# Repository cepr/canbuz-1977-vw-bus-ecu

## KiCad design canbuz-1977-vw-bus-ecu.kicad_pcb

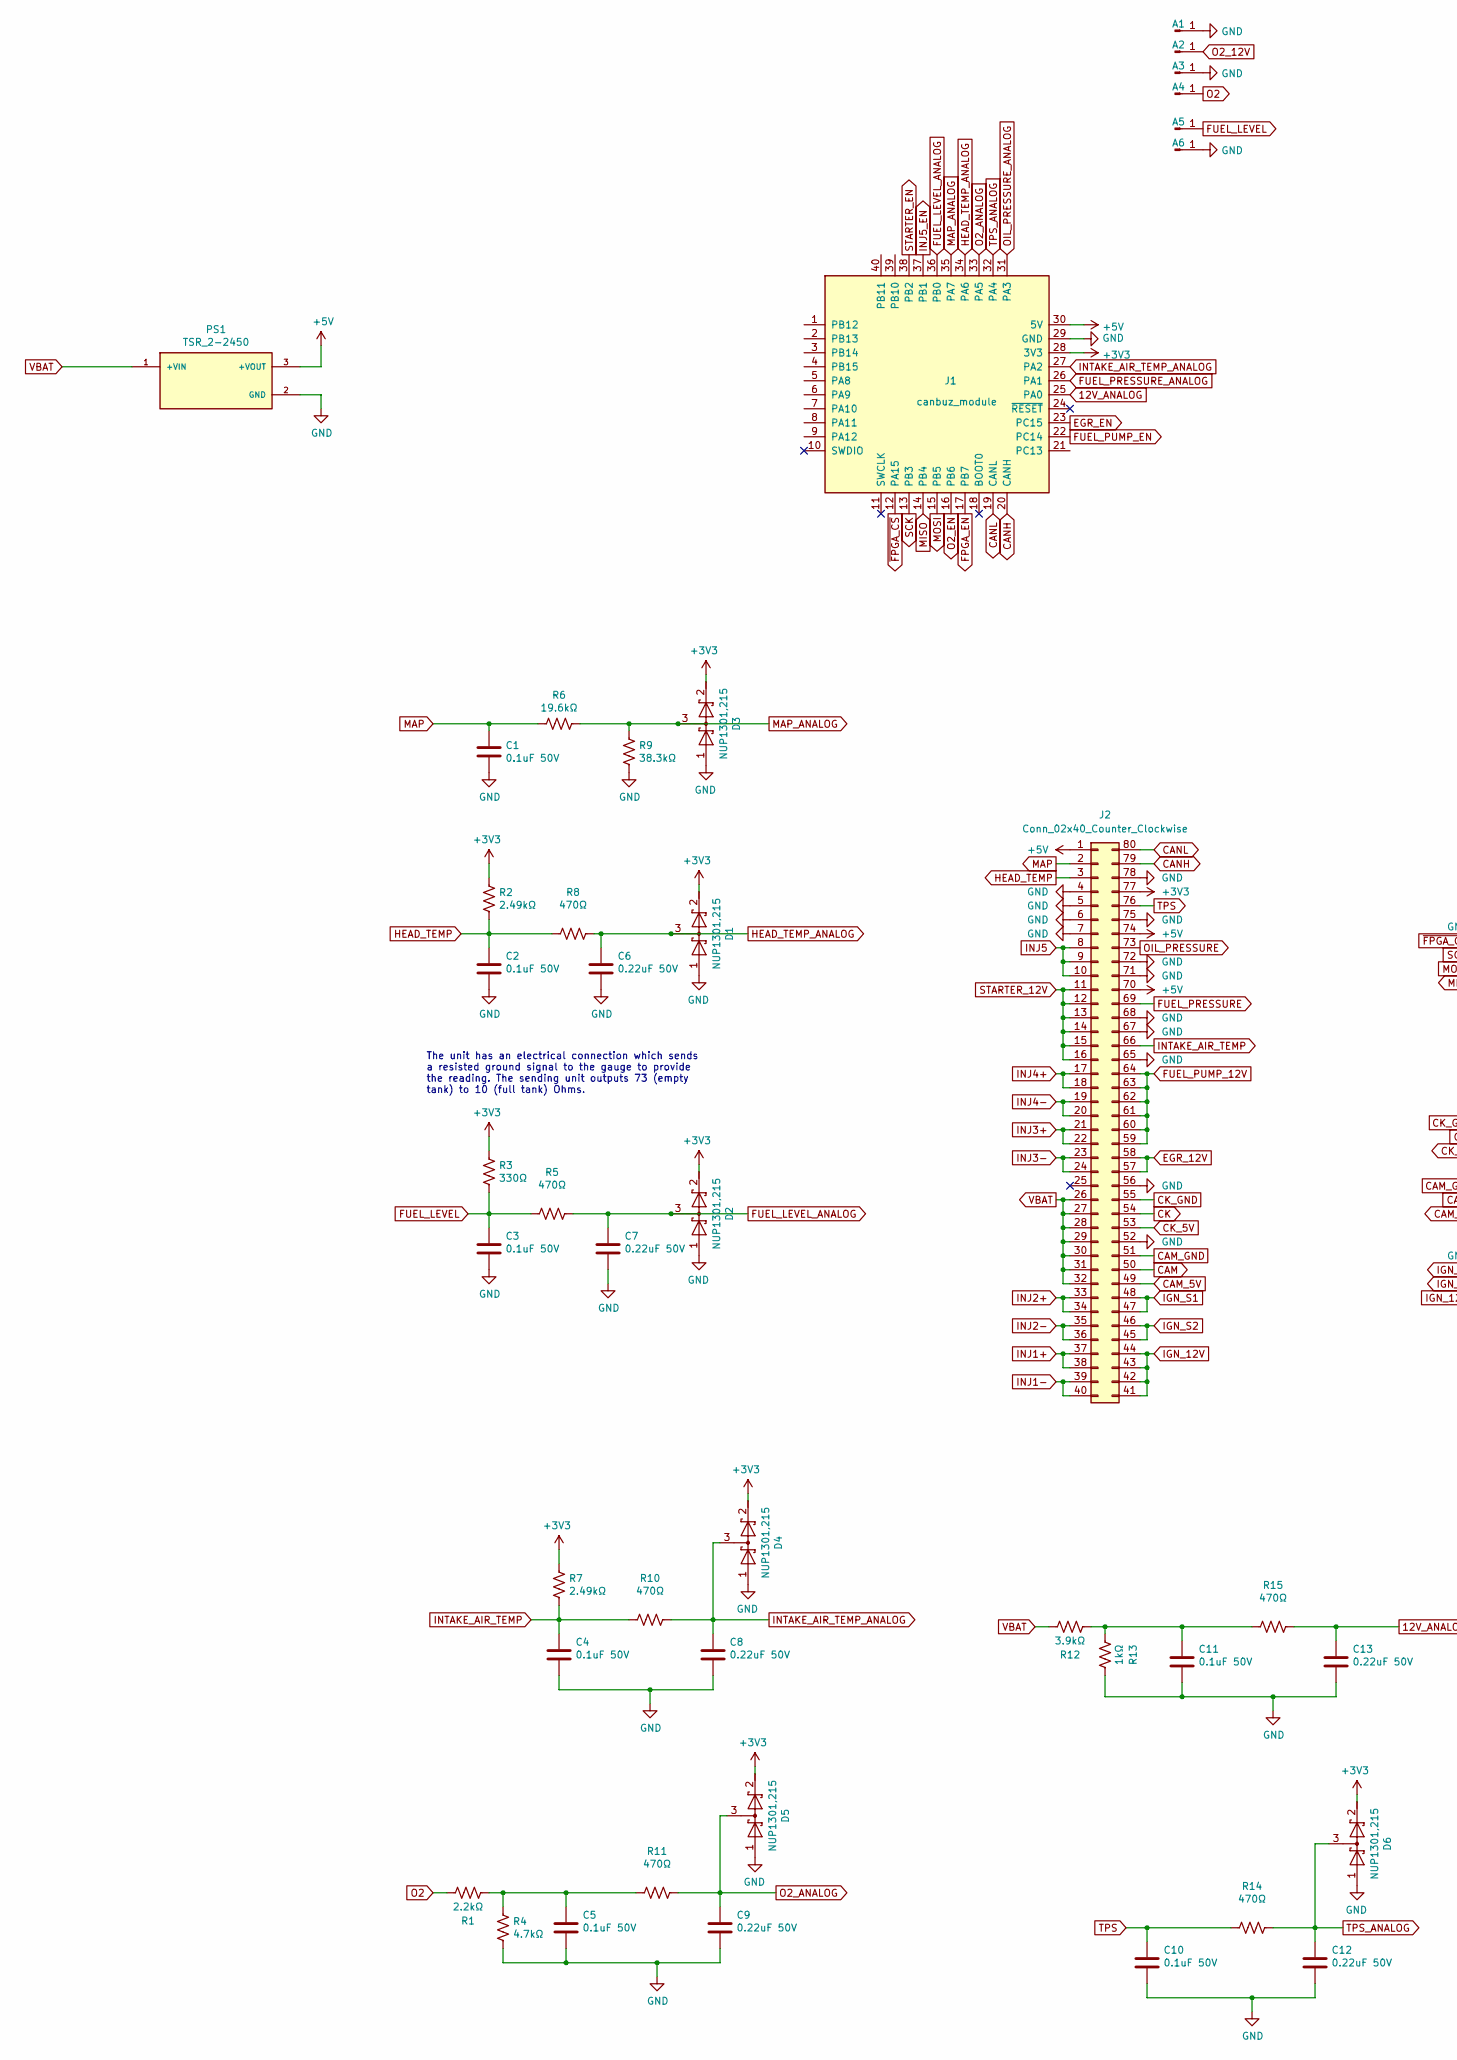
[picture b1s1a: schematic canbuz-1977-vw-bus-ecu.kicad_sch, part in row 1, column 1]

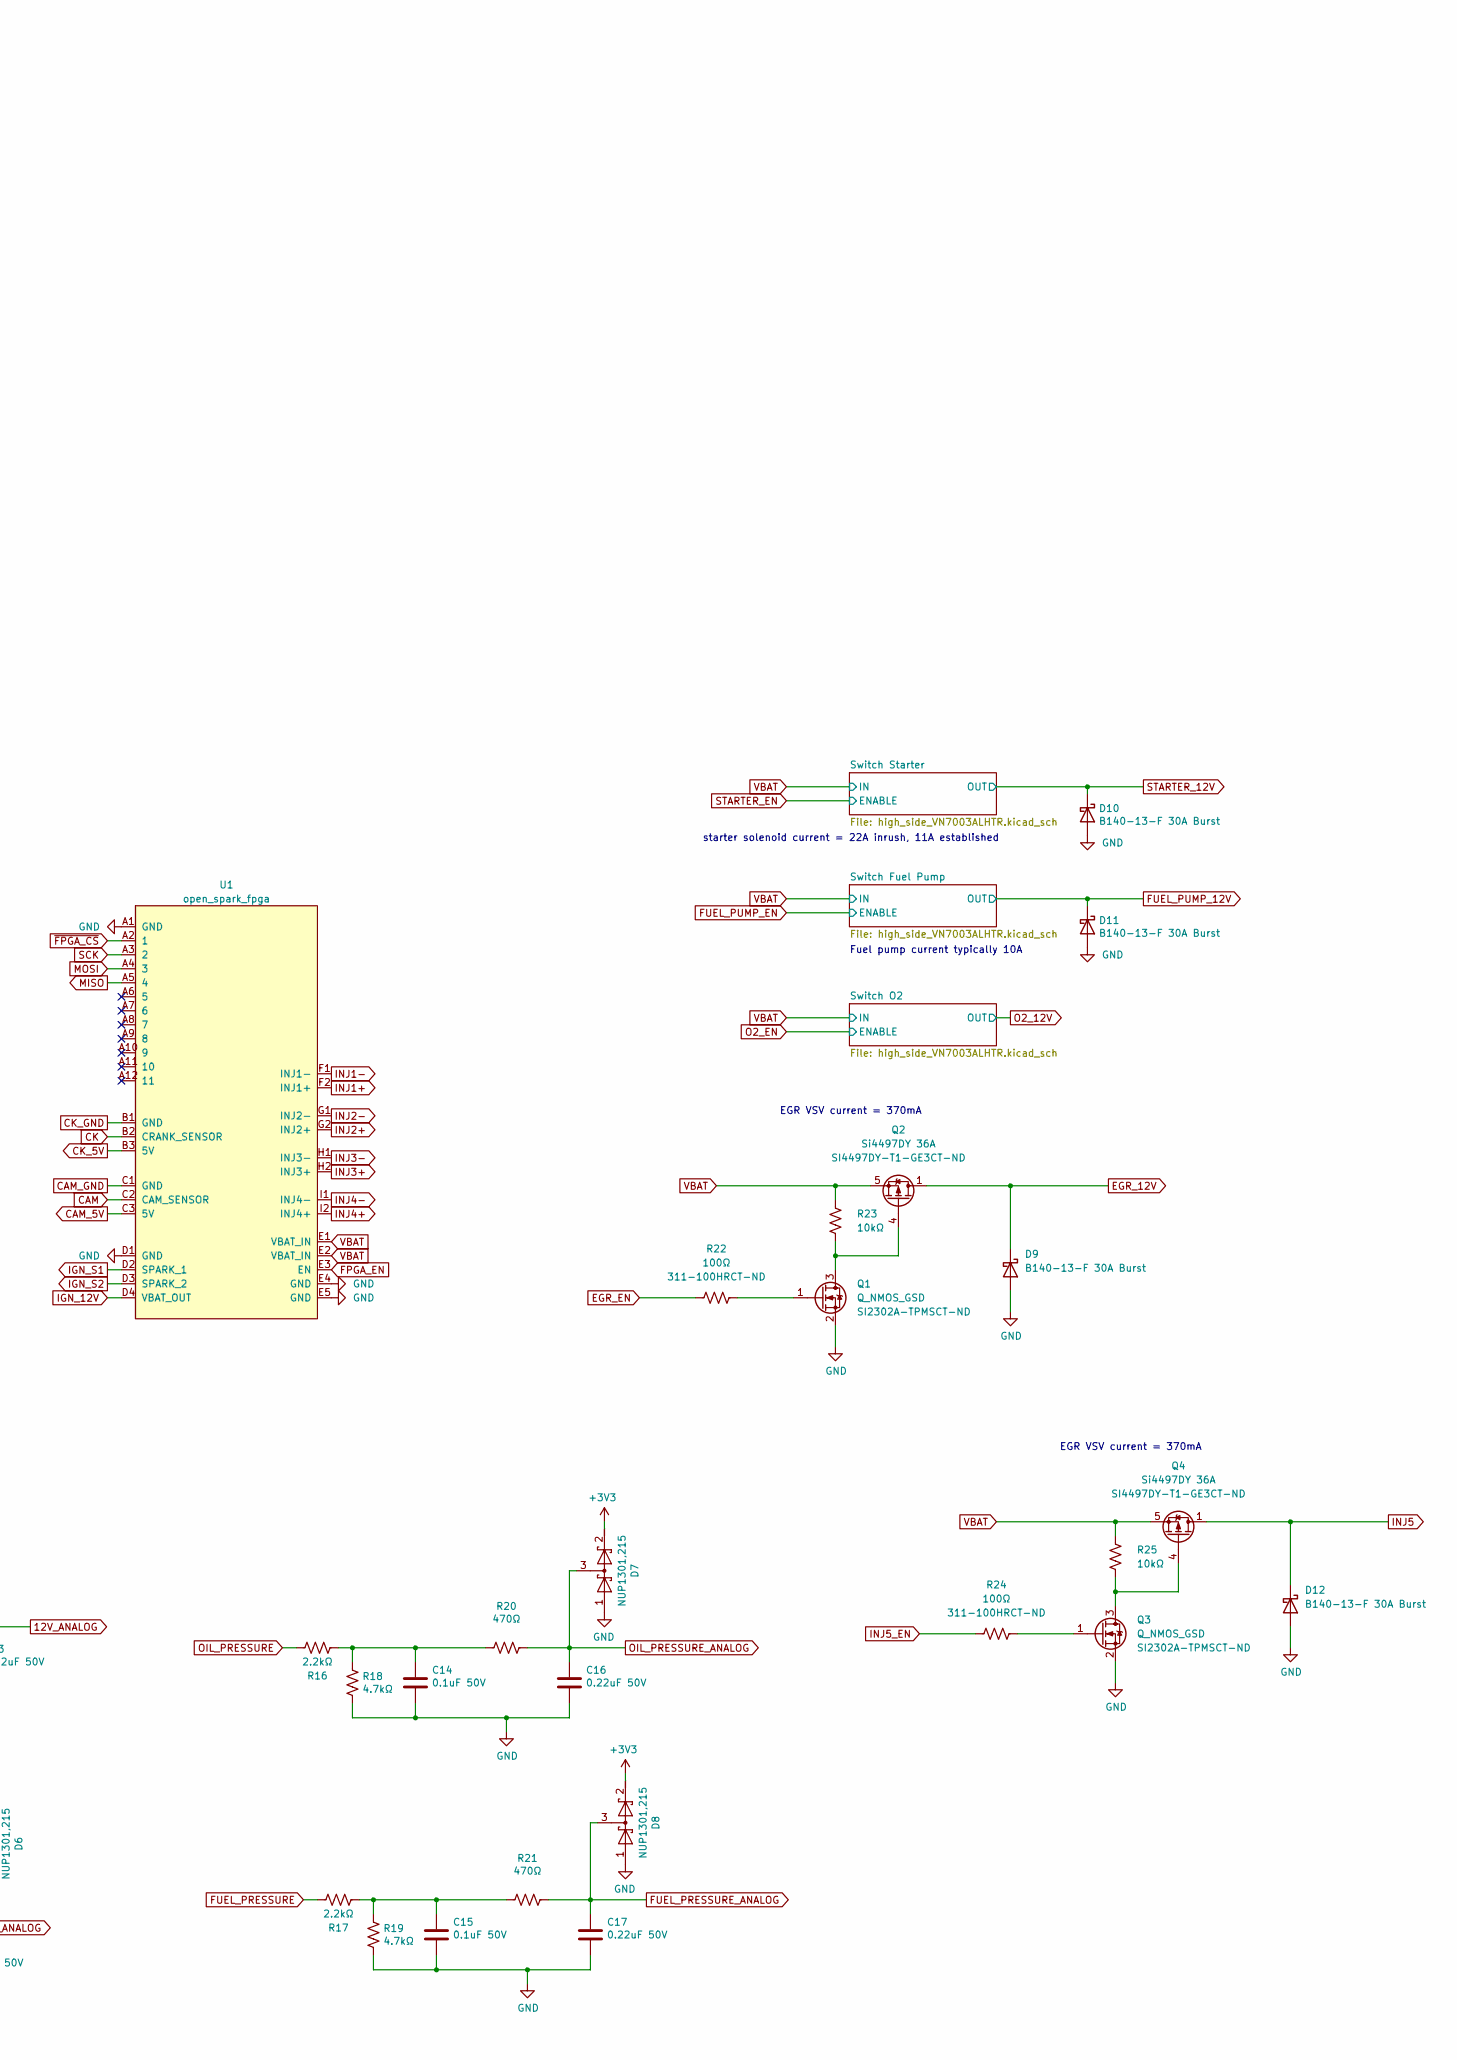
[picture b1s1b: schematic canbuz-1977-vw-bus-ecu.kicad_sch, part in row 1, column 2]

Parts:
A1, A2, A3, A4, A5, A6: Spade_Male
C1, C2, C3, C4, C5, C10, C11, C14, C15: 0.1uF 50V; C_0805_2012Metric_Pad1.18x1.45mm_HandSolder; Part KAF21BR71H104KT; DigiKey 478-6048-1-ND
C6, C7, C8, C9, C12, C13, C16, C17: 0.22uF 50V; C_0805_2012Metric_Pad1.18x1.45mm_HandSolder; Part CGA4J2X7R1H224K125AA; DigiKey 445-5683-1-ND
D1, D2, D3, D4, D5, D6, D7, D8: NUP1301,215; SOT-23; Part NUP1301,215; DigiKey 1727-5056-1-ND
D9, D10, D11, D12: B140-13-F 30A Burst; D_SMA; Part B340A-13-F
J1: canbuz_module; canbuz-module
J2: Conn_02x40_Counter_Clockwise; canbuz-1977-vw-bus-ecu-connector
PS1: TSR_2-2450; CONV_TSR_2-2450; Part TSR 2-2450; DigiKey 1951-2692-ND
Q1, Q3: Q_NMOS_GSD; SOT-23; Part SI2302A-TP; DigiKey SI2302A-TPMSCT-ND
Q2, Q4: Si4497DY 36A; SO-8_3.9x4.9mm_P1.27mm; Part SI4497DY-T1-GE3; DigiKey SI4497DY-T1-GE3CT-ND
R1, R16, R17: 2.2kΩ; R_0603_1608Metric_Pad0.98x0.95mm_HandSolder; Part ERJ-3GEYJ222V
R2, R7: 2.49kΩ; R_0603_1608Metric_Pad0.98x0.95mm_HandSolder; Part RK73H1JTTD2491F
R3: 330Ω; R_0603_1608Metric_Pad0.98x0.95mm_HandSolder
R4, R18, R19: 4.7kΩ; R_0603_1608Metric_Pad0.98x0.95mm_HandSolder; Part RC0603FR-074K7L
R5, R8, R10, R11, R14, R15, R20, R21: 470Ω; R_0603_1608Metric_Pad0.98x0.95mm_HandSolder; Part RC0603JR-07470RL
R6: 19.6kΩ; R_0603_1608Metric_Pad0.98x0.95mm_HandSolder; Part RC0603FR-0719K6L
R9: 38.3kΩ; R_0603_1608Metric_Pad0.98x0.95mm_HandSolder; Part RC0603FR-0738K3L
R12: 3.9kΩ; R_0603_1608Metric_Pad0.98x0.95mm_HandSolder; Part RC0603FR-073K9L
R13: 1kΩ; R_0603_1608Metric_Pad0.98x0.95mm_HandSolder; Part RC0603FR-071KL
R22, R24: 100Ω; R_0603_1608Metric_Pad0.98x0.95mm_HandSolder; Part RC0603FR-07100RL; DigiKey 311-100HRCT-ND
R23, R25: 10kΩ; R_0603_1608Metric_Pad0.98x0.95mm_HandSolder; Part RC0603FR-0710KL
U1: open_spark_fpga

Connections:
12V_ANALOG: C13.1, J1.25 (PA0), R15.1
+3V3: D1.2 (K), D2.2 (K), D3.2 (K), D4.2 (K), D5.2 (K), D6.2 (K), D7.2 (K), D8.2 (K), J1.28 (3V3), J2.77, R2.2, R3.2, R7.2
+5V: J1.30 (5V), J2.1, J2.70, J2.74, PS1.3 (+VOUT)
CAM: J2.50, U1.C2 (CAM_SENSOR)
CAM_5V: J2.49, U1.C3 (5V)
CAM_GND: J2.51, U1.C1 (GND)
CANH: J1.20 (CANH), J2.79
CANL: J1.19 (CANL), J2.80
CK: J2.54, U1.B2 (CRANK_SENSOR)
CK_5V: J2.53, U1.B3 (5V)
CK_GND: J2.55, U1.B1 (GND)
EGR_12V: D9.1 (K), J2.57, J2.58, Q2.1 (D), Q2.2 (D), Q2.3 (D)
EGR_EN: J1.23 (PC15), R22.1
FPGA_EN: J1.17 (PB7), U1.E3 (EN)
FUEL_LEVEL: A5.1, C3.1, R3.1, R5.2
FUEL_LEVEL_ANALOG: C7.1, D2.3 (common), J1.36 (PB0), R5.1
FUEL_PRESSURE: J2.69, R17.1
FUEL_PRESSURE_ANALOG: C17.1, D8.3 (common), J1.26 (PA1), R21.1
FUEL_PUMP_12V: D11.1 (K), J2.59, J2.60, J2.61, J2.62, J2.63, J2.64; also elsewhere on the board
FUEL_PUMP_EN: J1.22 (PC14); also elsewhere on the board
GND: A1.1, A3.1, A6.1, C1.2, C2.2, C3.2, C4.2, C5.2, C6.2, C7.2, C8.2, C9.2, C10.2, C11.2, C12.2, C13.2, C14.2, C15.2, C16.2, C17.2, D1.1 (A), D2.1 (A), D3.1 (A), D4.1 (A), D5.1 (A), D6.1 (A), D7.1 (A), D8.1 (A), D9.2 (A), D10.2 (A), D11.2 (A), D12.2 (A), J1.29 (GND), J2.4, J2.5, J2.6, J2.7, J2.52, J2.56, J2.65, J2.67, J2.68, J2.71, J2.72, J2.75, J2.78, PS1.2 (GND), Q1.2 (S), Q3.2 (S), R4.1, R9.2, R13.1, R18.1, R19.1, U1.A1 (GND), U1.D1 (GND), U1.E4 (GND), U1.E5 (GND); also elsewhere on the board
HEAD_TEMP: C2.1, J2.3, R2.1, R8.2
HEAD_TEMP_ANALOG: C6.1, D1.3 (common), J1.34 (PA6), R8.1
IGN_12V: J2.41, J2.42, J2.43, J2.44, U1.D4 (VBAT_OUT)
IGN_S1: J2.47, J2.48, U1.D2 (SPARK_1)
IGN_S2: J2.45, J2.46, U1.D3 (SPARK_2)
INJ1+: J2.37, J2.38, U1.F2 (INJ1+)
INJ1-: J2.39, J2.40, U1.F1 (INJ1-)
INJ2+: J2.33, J2.34, U1.G2 (INJ2+)
INJ2-: J2.35, J2.36, U1.G1 (INJ2-)
INJ3+: J2.21, J2.22, U1.H2 (INJ3+)
INJ3-: J2.23, J2.24, U1.H1 (INJ3-)
INJ4+: J2.17, J2.18, U1.I2 (INJ4+)
INJ4-: J2.19, J2.20, U1.I1 (INJ4-)
INJ5: D12.1 (K), J2.8, J2.9, J2.10, Q4.1 (D), Q4.2 (D), Q4.3 (D)
INJ5_EN: J1.37 (PB1), R24.1
INTAKE_AIR_TEMP: C4.1, J2.66, R7.1, R10.2
INTAKE_AIR_TEMP_ANALOG: C8.1, D4.3 (common), J1.27 (PA2), R10.1
MAP: C1.1, J2.2, R6.2
MAP_ANALOG: D3.3 (common), J1.35 (PA7), R6.1, R9.1
MISO: J1.14 (PB4), U1.A5 (4)
MOSI: J1.15 (PB5), U1.A4 (3)
unnamed: C5.1, R1.2, R4.2, R11.2
unnamed: C11.1, R12.2, R13.2, R15.2
unnamed: C14.1, R16.2, R18.2, R20.2
unnamed: C15.1, R17.2, R19.2, R21.2
unnamed: Q1.1 (G), R22.2
unnamed: Q1.3 (D), Q2.4 (G), R23.1
unnamed: Q3.1 (G), R24.2
unnamed: Q3.3 (D), Q4.4 (G), R25.1
O2: A4.1, R1.1
O2_12V: A2.1; also elsewhere on the board
O2_ANALOG: C9.1, D5.3 (common), J1.33 (PA5), R11.1
O2_EN: J1.16 (PB6); also elsewhere on the board
OIL_PRESSURE: J2.73, R16.1
OIL_PRESSURE_ANALOG: C16.1, D7.3 (common), J1.31 (PA3), R20.1
SCK: J1.13 (PB3), U1.A3 (2)
STARTER_12V: D10.1 (K), J2.11, J2.12, J2.13, J2.14, J2.15, J2.16; also elsewhere on the board
STARTER_EN: J1.38 (PB2); also elsewhere on the board
TPS: C10.1, J2.76, R14.2
TPS_ANALOG: C12.1, D6.3 (common), J1.32 (PA4), R14.1
VBAT: J2.26, J2.27, J2.28, J2.29, J2.30, J2.31, J2.32, PS1.1 (+VIN), Q2.5 (S), Q2.6 (S), Q2.7 (S), Q2.8 (S), Q4.5 (S), Q4.6 (S), Q4.7 (S), Q4.8 (S), R12.1, R23.2, R25.2, U1.E1 (VBAT_IN), U1.E2 (VBAT_IN); also elsewhere on the board
~FPGA_CS: J1.12 (PA15), U1.A2 (1)

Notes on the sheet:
EGR VSV current = 370mA
The unit has an electrical connection which sends a resisted ground signal to the gauge to provide the reading. The sending unit outputs 73 (empty tank) to 10 (full tank) Ohms.
starter solenoid current = 22A inrush, 11A established
Fuel pump current typically 10A

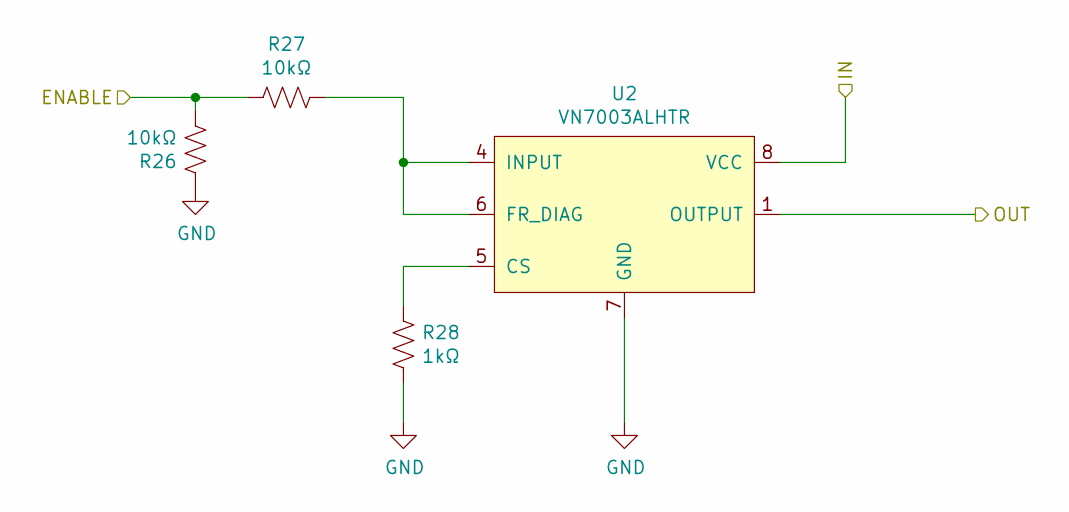
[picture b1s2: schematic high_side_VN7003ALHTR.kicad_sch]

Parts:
R26, R27: 10kΩ; R_0603_1608Metric_Pad0.98x0.95mm_HandSolder; Part RC0603FR-0710KL
R28: 1kΩ; R_0603_1608Metric_Pad0.98x0.95mm_HandSolder; Part RC0603FR-071KL
U2: VN7003ALHTR; OctaPAK_7_1; Part VN7003AHTR; DigiKey 497-16716-1-ND

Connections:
GND: R26.2, R28.1, U2.7 (GND); also elsewhere on the board
unnamed: R27.1, U2.4 (INPUT), U2.6 (FR_DIAG)
unnamed: R28.2, U2.5 (CS)
STARTER_12V: U2.1 (OUTPUT), U2.2 (OUTPUT), U2.3 (OUTPUT); also elsewhere on the board
STARTER_EN: R26.1, R27.2; also elsewhere on the board
VBAT: U2.8 (VCC); also elsewhere on the board

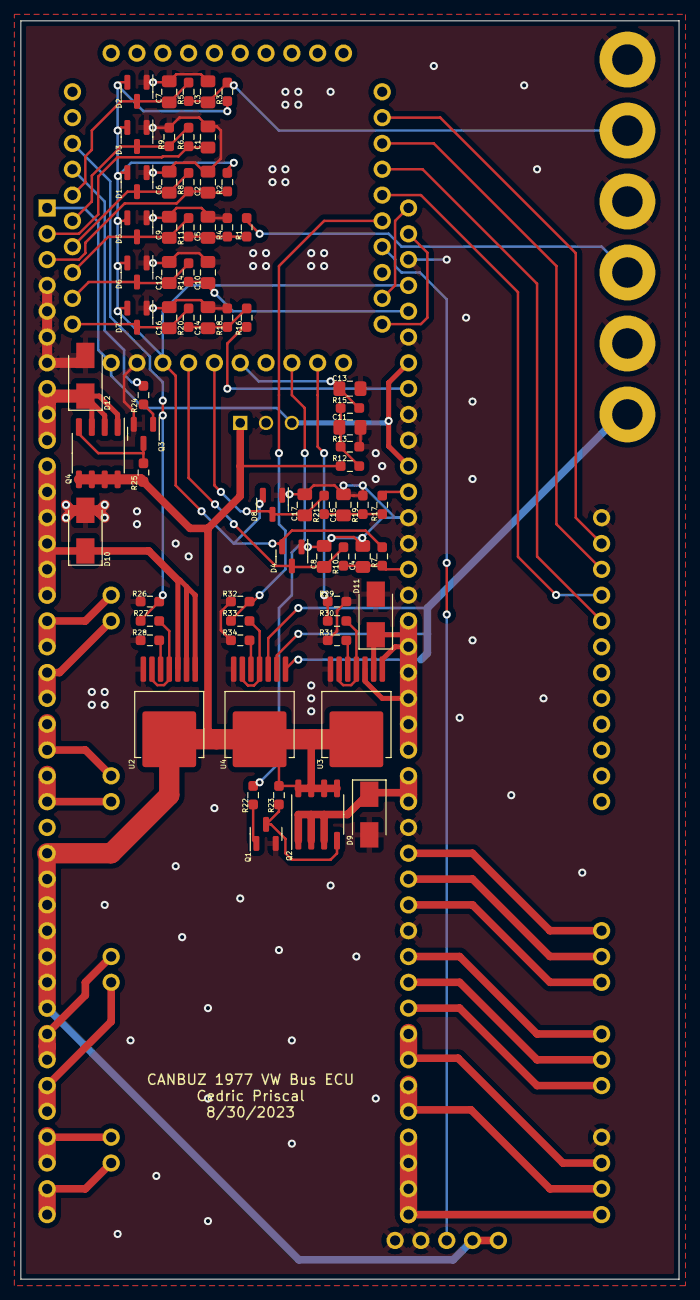
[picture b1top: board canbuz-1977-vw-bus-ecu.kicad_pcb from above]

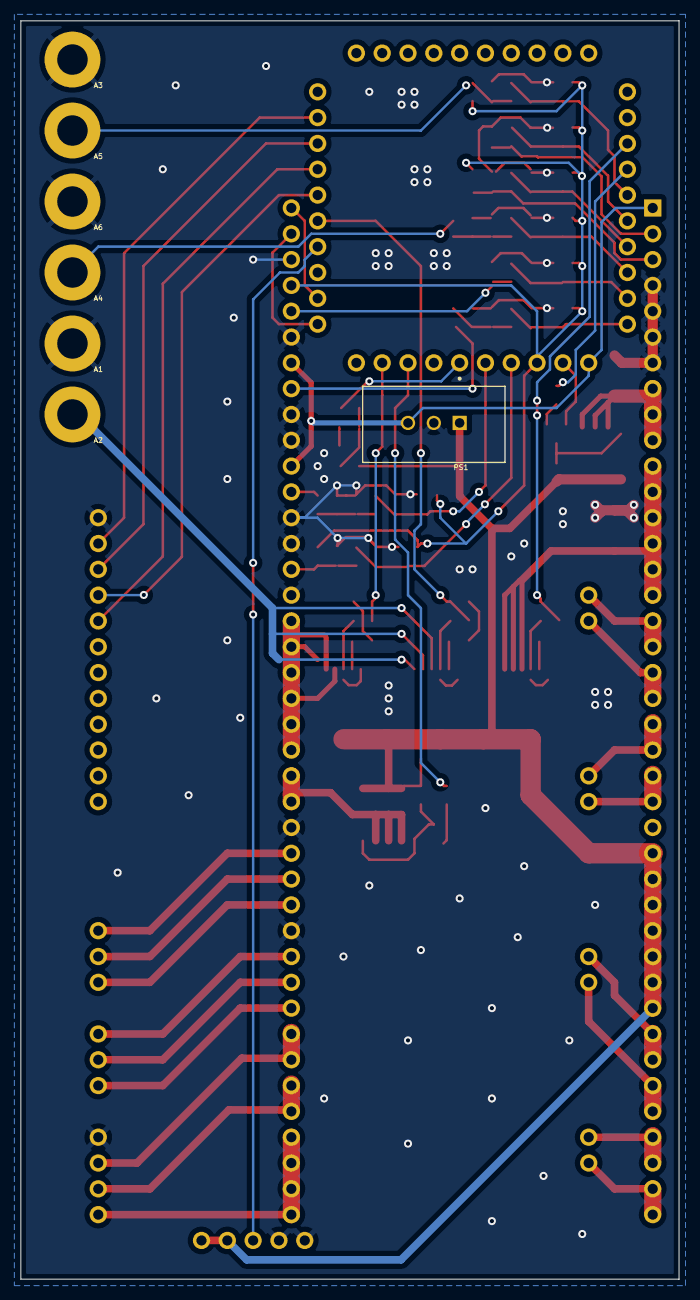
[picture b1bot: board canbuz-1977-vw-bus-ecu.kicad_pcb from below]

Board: 2 copper layers, 64.8 x 123.8 mm, 80 parts (9 on the bottom side), 69 nets.

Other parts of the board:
R29, R30, R32, R33: 10kΩ; R_0603_1608Metric_Pad0.98x0.95mm_HandSolder
R31, R34: 1kΩ; R_0603_1608Metric_Pad0.98x0.95mm_HandSolder
U3, U4: VN7003ALHTR; OctaPAK_7_1

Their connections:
FUEL_PUMP_12V: U3.1 (OUTPUT), U3.2 (OUTPUT), U3.3 (OUTPUT); also elsewhere on the board
FUEL_PUMP_EN: R29.1, R30.2; also elsewhere on the board
GND: R29.2, R31.1, R32.2, R34.1, U3.7 (GND), U4.7 (GND); also elsewhere on the board
unnamed: R30.1, U3.4 (INPUT), U3.6 (FR_DIAG)
unnamed: R31.2, U3.5 (CS)
unnamed: R33.1, U4.4 (INPUT), U4.6 (FR_DIAG)
unnamed: R34.2, U4.5 (CS)
O2_12V: U4.1 (OUTPUT), U4.2 (OUTPUT), U4.3 (OUTPUT); also elsewhere on the board
O2_EN: R32.1, R33.2; also elsewhere on the board
VBAT: U3.8 (VCC), U4.8 (VCC); also elsewhere on the board

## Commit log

2023-07-15 Rev 1.0
2023-08-31 rev 08/30/2023
